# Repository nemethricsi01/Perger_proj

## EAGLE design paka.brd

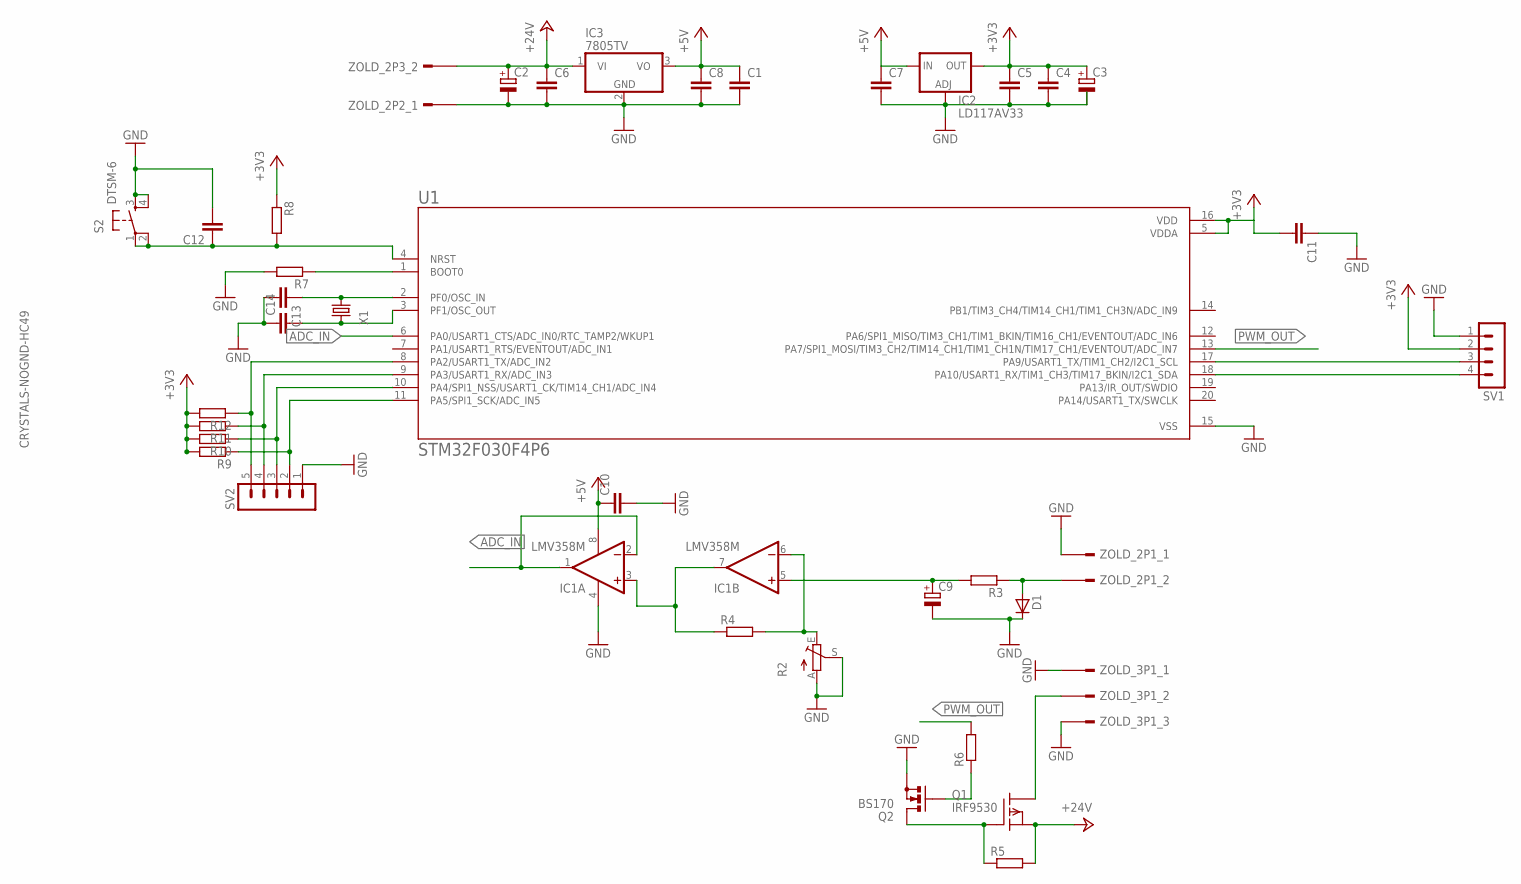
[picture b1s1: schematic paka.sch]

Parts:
C1, C4, C5, C6, C7, C8, C10, C11, C12, C13, C14: C-EUC0805; C0805
C2: CPOL-EUE3.5-8; E3,5-8
C3, C9: CPOL-EUE2.5-6; E2,5-6
D1: D0805
IC1: LMV358M; SO08
IC2: LD117AV33; TO220L1
IC3: 7805TV; TO220V
Q1: IRF9530; TO220
Q2: BS170; SOT54E
R2: TRIM_EU-PT10; PT-10
R3, R4, R5, R6, R7, R8, R9, R10, R11, R12: R-EU_R0805; R0805
S2: DTSM-6
SV1: MA04-1
SV2: MA05-1
U1: STM32F030F4P6; SOP65P640X120-20N
X1: CRYSTALS-NOGND-HC49; HC49
ZOLD_2P1, ZOLD_2P2, ZOLD_2P3: ZOLD_KICSI_2PFEKVO; ZOLD_KICSI_2P_FEKVO
ZOLD_3P1: ZOLD_KICSI_3PFEKVŐ; ZOLD_KICSI_3P_FEKVO

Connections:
+3V3: C3.+, C4.1, C5.1, C11.2, IC2.2 (OUT), R8.1, R9.2, R10.2, R11.2, R12.2, SV1.2, U1.5 (VDDA), U1.16 (VDD)
+5V: C1.1, C7.1, C8.1, C10.1, IC1.8 (V+), IC2.3 (IN), IC3.3 (VO)
+24V: C2.+, C6.1, IC3.1 (VI), Q1.3 (S), R5.2, ZOLD_2P3.2
ADC_IN: IC1.1 (OUT), IC1.2 (-IN), U1.6 (PA0/USART1_CTS/ADC_IN0/RTC_TAMP2/WKUP1)
GND: C1.2, C2.-, C4.2, C5.2, C6.2, C7.2, C8.2, C9.-, C10.2, C11.1, C12.2, C13.2, C14.1, D1.2 (C), IC1.4 (V-), IC2.1 (ADJ), IC3.2 (GND), Q2.S, R2.A, R2.S, R7.2, S2.3, S2.4, SV1.1, SV2.1, U1.15 (VSS), ZOLD_2P1.1, ZOLD_2P2.1, ZOLD_3P1.1, ZOLD_3P1.3
unnamed: D1.1 (A), R3.1, ZOLD_2P1.2
unnamed: C9.+, IC1.5 (+IN), R3.2
unnamed: IC1.6 (-IN), R2.E, R4.2
unnamed: Q1.2 (D), ZOLD_3P1.2
unnamed: IC1.3 (+IN), IC1.7 (OUT), R4.1
unnamed: Q1.1 (G), Q2.D, R5.1
unnamed: Q2.G, R6.1
unnamed: R9.1, SV2.2, U1.11 (PA5/SPI1_SCK/ADC_IN5)
unnamed: R7.1, U1.1 (BOOT0)
unnamed: C12.1, R8.2, S2.1, S2.2, U1.4 (NRST)
unnamed: R10.1, SV2.3, U1.10 (PA4/SPI1_NSS/USART1_CK/TIM14_CH1/ADC_IN4)
unnamed: R11.1, SV2.4, U1.9 (PA3/USART1_RX/ADC_IN3)
unnamed: C13.1, U1.2 (PF0/OSC_IN), X1.1
unnamed: C14.2, U1.3 (PF1/OSC_OUT), X1.2
unnamed: R12.1, SV2.5, U1.8 (PA2/USART1_TX/ADC_IN2)
unnamed: SV1.3, U1.17 (PA9/USART1_TX/TIM1_CH2/I2C1_SCL)
unnamed: SV1.4, U1.18 (PA10/USART1_RX/TIM1_CH3/TIM17_BKIN/I2C1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)
PWM_OUT: R6.2, U1.13 (PA7/SPI1_MOSI/TIM3_CH2/TIM14_CH1/TIM1_C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)

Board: 2 copper layers, 40 parts (0 on the bottom side), 23 nets, no tracks yet.

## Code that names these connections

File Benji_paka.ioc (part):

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Mcu.Name=STM32F030F4Px
Mcu.Package=TSSOP20
Mcu.UserName=STM32F030F4Px
PA0.Mode=IN0
PA0.Signal=ADC_IN0
PA10.Mode=I2C
PA10.Signal=I2C1_SDA
PA13.Mode=Serial_Wire
PA13.Signal=SYS_SWDIO
PA14.Mode=Serial_Wire
PA14.Signal=SYS_SWCLK
PA2.GPIOParameters=GPIO_PuPd
PA2.GPIO_PuPd=GPIO_NOPULL
PA2.Signal=GPIO_Input
PA3.Signal=GPIO_Input
PA4.Signal=GPIO_Input
PA5.Signal=GPIO_Input
PA7.Signal=S_TIM3_CH2
PA9.Mode=I2C
PA9.Signal=I2C1_SCL
PF0-OSC_IN.Mode=HSE-External-Oscillator
PF0-OSC_IN.Signal=RCC_OSC_IN
PF1-OSC_OUT.Mode=HSE-External-Oscillator
PF1-OSC_OUT.Signal=RCC_OSC_OUT
RCC.HSE_VALUE=16000000
RCC.SYSCLKFreq_VALUE=48000000
RCC.SYSCLKSource=RCC_SYSCLKSOURCE_PLLCLK
board=custom

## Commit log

2020-09-04 added kerdesek.txt
2020-09-12 kiegészítés, átbeszélés
2020-09-12 kép is lett
2020-10-17 kapcsrajz lett
2020-10-17 pédéef is lett
2020-11-27 source code added
2020-11-27 new pdf
